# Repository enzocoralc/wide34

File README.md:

# wide34

⚠️ If you've used the gerbers to fab before 2022/2/4 you'll need to bodge wire the middle TRRS pin (which was connected to P15) to P1 and the inner bottom key side pin (which was connected to P1) to P15.

split 34 keys with 21mm X pitch and chopped chocs for less vertical movement. 
It's promicro compatible and supports only chocs.
Designed in ergogen. You can use this wonderful tool [here](https://ergogen.xyz/). Disclaimer: the ergogen file here does not output the same edgecuts as the final pcb.

Left side

 Right side

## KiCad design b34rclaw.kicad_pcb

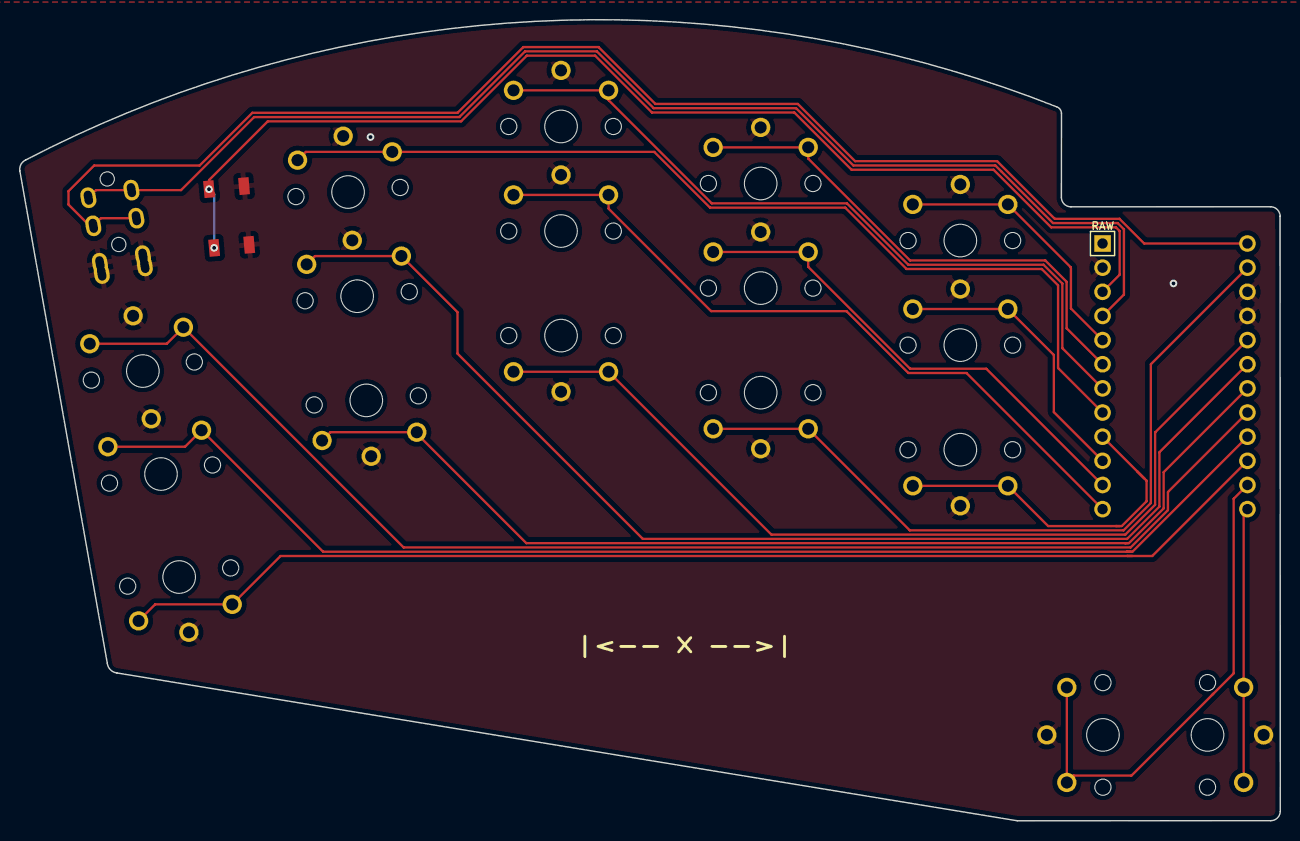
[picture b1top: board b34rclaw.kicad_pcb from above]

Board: 2 copper layers, 132.6 x 84.3 mm, 20 parts (0 on the bottom side), 19 nets.

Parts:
B1, B2: SW_TACT_ALPS_SKQGABE010
MCU1: ProMicro
S1, S2, S3, S4, S5, S6, S7, S8, S9, S10, S11, S12, S13, S14, S15, S16, S17: PG1350

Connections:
GND: B1.2, B2.2, MCU1.2, MCU1.15, MCU1.16, S1.2, S2.2, S3.2, S4.2, S5.2, S6.2, S7.2, S8.2, S9.2, S10.2, S11.2, S12.2, S13.2, S14.2, S15.2, S16.2, S17.2
P0: MCU1.14, S10.1
P2: MCU1.17, S7.1
P3: MCU1.18, S5.1
P4: MCU1.19, S4.1
P5: MCU1.20, S3.1
P6: MCU1.21, S2.1
P7: MCU1.22, S1.1
P8: MCU1.23, S16.1
P9: MCU1.24, S17.1
P10: MCU1.12, S8.1
P14: MCU1.10, S14.1
P15: MCU1.9, S13.1
P16: MCU1.11, S11.1
P18: MCU1.8, S6.1
P19: MCU1.7, S9.1
P20: MCU1.6, S12.1
P21: MCU1.5, S15.1
RST: B1.1, B2.1, MCU1.3

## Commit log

2021-12-29 added everything
2022-02-04 fixed trrs wiring
2022-02-04 added warning for earlier pcb design
